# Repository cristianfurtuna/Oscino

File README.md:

# OSCINO - Osciloscop digital interfațat USB cu intrare izolată galvanic
Proiectul nostru constă într-un osciloscop digital interfațat prin USB, capabil să achiziționeze, să proceseze și să afișeze semnale electrice în timp real pe PC.
## Specificații
- in: 5V DC USB-C;<br>
- out: >2 Mbit/s serial UART data;<br>
- Arduino Mega compatible pinout
- sampling rate: ~300 ksa/s;<br>
- AC/DC coupling;<br>
- Galvanically Isolated Frontend with Differential Signal Aquisition;<br>
- 0...230V AC/DC input range using different attenuation stages;<br>
- Attenuator for High Input Voltages;<br>
- UI for PC use;<br>
- timebase and synchronisation (trigger).<br>
## Elaborare etape
- [x] Alegere componente<br>
- [x] Schemă electrică<br>
- [x] Cablaj<br>
- [x] Prototip<br>
- [x] Programare uC<br>
- [x] Programare UI<br>
- [x] Testare<br>
- [x] Elaborare documentație<br>
- [x] Realizare prezentare PowerPoint<br>
## Alegerea unui microcontroller potrivit
- [ ] C8051F120 -> preț: $11.22<br>
- [ ] STM32H743ZIT6 -> preț: $15.23<br>
- [ ] MIMXRT1062DVL6B -> preț: $12.00<br>
- [x] ATMEGA 2560 -> preț: $10.56<br>
## Asamblarea PCB-ului la fabrică este mult prea scumpă pentru a finaliza cablajul (TBD asamblare manuală)

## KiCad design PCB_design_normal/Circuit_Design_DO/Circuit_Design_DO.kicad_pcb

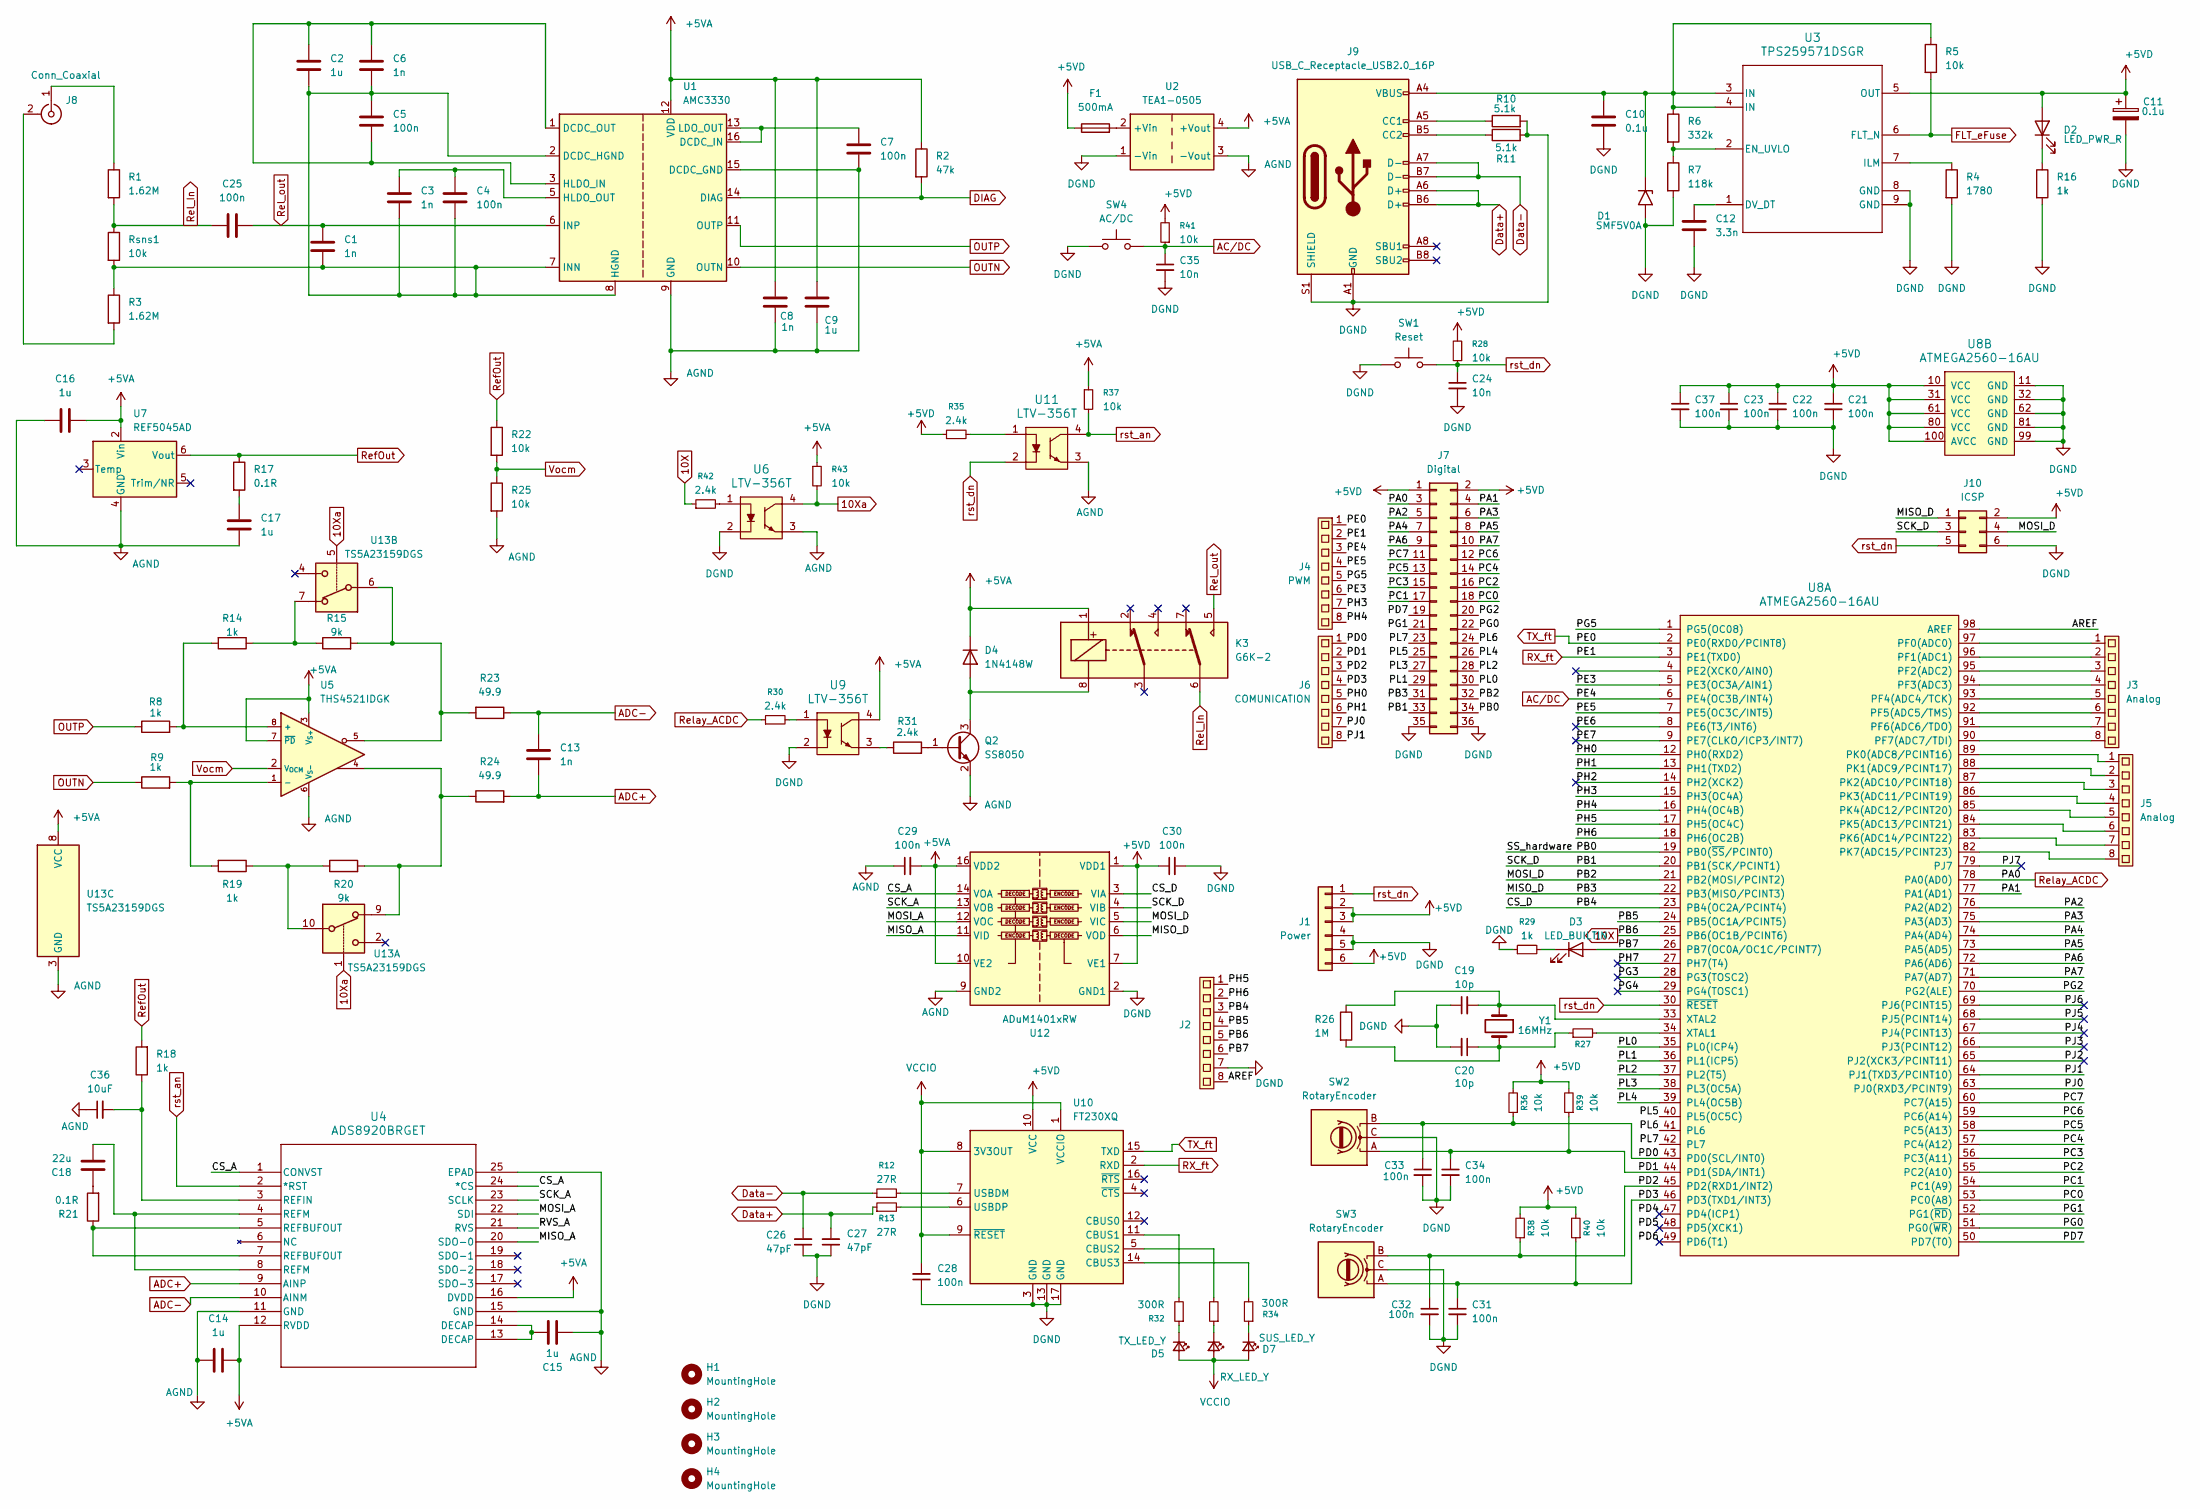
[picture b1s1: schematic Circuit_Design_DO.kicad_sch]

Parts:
C1: 1n; C_0805_2012Metric; JLCPCB Part # C1710
C2, C9, C14, C15, C16, C17: 1u; C_0805_2012Metric; JLCPCB Part # C1712
C3, C6, C8, C13: 1n; C_0805_2012Metric; JLCPCB Part # C1791
C4, C5, C7, C21, C22, C23, C25, C28, C29, C30, C31, C32, C33, C34, C37: 100n; C_0805_2012Metric; JLCPCB Part # C1711
C10, C11: 0.1u; C_0805_2012Metric; JLCPCB Part # C1711
C12: 3.3n; C_0805_2012Metric; JLCPCB Part # C1738
C18: 22u; C_0805_2012Metric; JLCPCB Part # C5674
C19, C20: 10p; C_0805_2012Metric; JLCPCB Part # C107107
C24, C35: 10n; C_0805_2012Metric; JLCPCB Part # C1804
C26, C27: 47pF; C_0805_2012Metric; JLCPCB Part # C14857
C36: 10uF; CP_EIA-6032-28_Kemet-C; JLCPCB Part # C7209
D1: SMF5V0A; D_SMF; JLCPCB Part # C1972946
D2: LED_PWR_R; LED_0805_2012Metric; JLCPCB Part # C86865
D3: LED_BUILTIN; LED_0805_2012Metric; JLCPCB Part # C2904378
D4: 1N4148W; D_SOD-123; JLCPCB Part # C2099
D5: TX_LED_Y; LED_0805_2012Metric; JLCPCB Part # C2904378
D6: RX_LED_Y; LED_0805_2012Metric; JLCPCB Part # C2904378
D7: SUS_LED_Y; LED_0805_2012Metric; JLCPCB Part # C2904378
F1: 500mA; Fuse_0805_2012Metric; JLCPCB Part # C20977
H1, H2, H3, H4: MountingHole; MountingHole_3.2mm_M3_DIN965_Pad_TopBottom
J1: Power; PinHeader_1x06_P2.54mm_Vertical
J2: PinHeader_1x08_P2.54mm_Vertical
J3, J5: Analog; PinHeader_1x08_P2.54mm_Vertical
J4: PWM; PinHeader_1x08_P2.54mm_Vertical
J6: COMUNICATION; PinHeader_1x08_P2.54mm_Vertical
J7: Digital; PinHeader_2x18_P2.54mm_Vertical
J8: Conn_Coaxial; BNC_Amphenol_B6252HB-NPP3G-50_Horizontal; JLCPCB Part # C2837587
J9: USB_C_Receptacle_USB2.0_16P; USB_C_Receptacle_GCT_USB4105-xx-A_16P_TopMnt_Horizontal; JLCPCB Part # C393939
J10: ICSP; PinHeader_2x03_P2.54mm_Vertical
K3: G6K-2; Relay_DPDT_Omron_G6K-2F-Y; JLCPCB Part # C2982926
Q2: SS8050; SOT-23; JLCPCB Part # C2150
R1, R3: 1.62M; R_0805_2012Metric; JLCPCB Part # C189667
R2: 47k; R_0805_2012Metric; JLCPCB Part # C702826
R4: 1780; R_0805_2012Metric; JLCPCB Part # C17397
R5, R22, R25, R28, R36, R37, R38, R39, R40, R41, R43: 10k; R_0805_2012Metric; JLCPCB Part # C702829
R6: 332k; R_0805_2012Metric; JLCPCB Part # C17631
R7: 118k; R_0805_2012Metric; JLCPCB Part # C17427
R8, R9, R14, R16, R18, R19, R29: 1k; R_0805_2012Metric; JLCPCB Part # C702831
R10, R11: 5.1k; R_0805_2012Metric; JLCPCB Part # C702837
R12, R13, R27: 27R; R_0805_2012Metric; JLCPCB Part # C17594
R15, R20: 9k; R_0805_2012Metric; JLCPCB Part # C247026
R17, R21: 0.1R; R_0805_2012Metric; JLCPCB Part # C125639
R23, R24: 49.9; R_0805_2012Metric; JLCPCB Part # C17720
R26: 1M; R_0805_2012Metric; JLCPCB Part # C17514
R30, R31, R35, R42: 2.4k; R_0805_2012Metric; JLCPCB Part # C22370006
R32, R33, R34: 300R; R_0805_2012Metric; JLCPCB Part # C22356757
Rsns1: 10k; R_0805_2012Metric; JLCPCB Part # C702829
SW1: Reset; Switch_Tactile_SMD_6x6mm; JLCPCB Part # C2845322
SW2, SW3: RotaryEncoder; RotaryEncoder_Alps_EC11E_Vertical_H20mm; JLCPCB Part # C370986
SW4: AC/DC; Switch_Tactile_SMD_6x6mm; JLCPCB Part # C2845322
U1: AMC3330; SOIC-16W_7.5x10.3mm_P1.27mm; JLCPCB Part # C5214212
U2: TEA1-0505; Converter_DCDC_TRACO_TEA1-xxxx_THT; JLCPCB Part # C5291394
U3: TPS259571DSGR; DSG0008A; JLCPCB Part # C471038
U4: ADS8920BRGET; RGE24_2P7X2P7_TEX; JLCPCB Part # C1542899
U5: THS4521IDGK; VSSOP-8_3x3mm_P0.65mm; JLCPCB Part # C170157
U6, U9, U11: LTV-356T; SMD-4_4.4x3.85mm_P2.54mm; MPN LTV-356T; Digi-Key_PN 160-1337-1-ND
U7: REF5045AD; SOIC-8_3.9x4.9mm_P1.27mm; JLCPCB Part # C1575525
U8: ATMEGA2560-16AU; TQFP-100_14x14mm; MPN ATMEGA2560-16AU; Digi-Key_PN ATMEGA2560-16AU-ND
U10: FT230XQ; QFN-16-1EP_4x4mm_P0.65mm_EP2.1x2.1mm; JLCPCB Part # C128629
U12: ADuM1401xRW; SOIC-16W_7.5x10.3mm_P1.27mm; JLCPCB Part # C33273
U13: TS5A23159DGS; VSSOP-10_3x3mm_P0.5mm; JLCPCB Part # C42751
Y1: 16MHz; Crystal_SMD_5032-2Pin_5.0x3.2mm; JLCPCB Part # C242221

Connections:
10X: J2.5, R42.1, U8.25 (PB6(OC1B/PCINT6))
10Xa: R43.2, U6.4, U13.1, U13.5
+5VA: C8.1, C9.1, C14.2, C16.1, C29.2, D4.1 (K), K3.1, R2.1, R37.1, R43.1, U1.12 (VDD), U2.4 (+Vout), U4.12 (RVDD), U4.16 (DVDD), U5.3 (V_{S+}), U5.7 (~PD), U7.2 (Vin), U9.4, U12.10 (VE2), U12.16 (VDD2), U13.8 (VCC); also elsewhere on the board
+5VD: C11.1, C21.1, C22.1, C23.1, C30.1, C37.1, D2.2 (A), F1.1, J1.2, J1.3, J1.6, J7.1, J7.2, J10.2, R28.2, R35.1, R36.2, R38.2, R39.2, R40.2, R41.2, U3.5 (OUT), U8.10 (VCC), U8.31 (VCC), U8.61 (VCC), U8.80 (VCC), U8.100 (AVCC), U10.10 (VCC), U12.1 (VDD1), U12.7 (VE1)
/AREF: J2.8, U8.98 (AREF)
/CS_A: U4.1 (CONVST), U4.24 (*CS), U12.14 (VOA)
/CS_D: J2.3, U8.23 (PB4(OC2A/PCINT4)), U12.3 (VIA)
/MISO_A: U4.20 (SDO-0), U12.11 (VID)
/MISO_D: J7.31, J10.1, U8.22 (PB3(MISO/PCINT3)), U12.6 (VOD)
/MOSI_A: U4.22 (SDI), U12.12 (VOC)
/MOSI_D: J7.32, J10.4, U8.21 (PB2(MOSI/PCINT2)), U12.5 (VIC)
/PA1: J7.4, U8.77 (PA1(AD1))
/PA2: J7.5, U8.76 (PA2(AD2))
/PA3: J7.6, U8.75 (PA3(AD3))
/PA4: J7.7, U8.74 (PA4(AD4))
/PA5: J7.8, U8.73 (PA5(AD5))
/PA6: J7.9, U8.72 (PA6(AD6))
/PA7: J7.10, U8.71 (PA7(AD7))
/PB0: J7.34, U8.19 (PB0(~SS/PCINT0))
/PB1: J7.33, J10.3, U8.20 (PB1(SCK/PCINT1)), U12.4 (VIB)
/PB5: J2.4, U8.24 (PB5(OC1A/PCINT5))
/PB7: D3.2 (A), J2.6, U8.26 (PB7(OC0A/OC1C/PCINT7))
/PC0: J7.18, U8.53 (PC0(A8))
/PC1: J7.17, U8.54 (PC1(A9))
/PC2: J7.16, U8.55 (PC2(A10))
/PC3: J7.15, U8.56 (PC3(A11))
/PC4: J7.14, U8.57 (PC4(A12))
/PC5: J7.13, U8.58 (PC5(A13))
/PC6: J7.12, U8.59 (PC6(A14))
/PC7: J7.11, U8.60 (PC7(A15))
/PD0: C33.1, J6.1, R36.1, SW2.B, U8.43 (PD0(SCL/INT0))
/PD1: C34.1, J6.2, R39.1, SW2.A, U8.44 (PD1(SDA/INT1))
/PD2: C32.1, J6.3, R38.1, SW3.B, U8.45 (PD2(RXD1/INT2))
/PD3: C31.1, J6.4, R40.1, SW3.A, U8.46 (PD3(TXD1/INT3))
/PD4: U8.47 (PD4(ICP1))
/PD5: U8.48 (PD5(XCK1))
/PD6: U8.49 (PD6(T1))
/PD7: J7.19, U8.50 (PD7(T0))
/PE3: J4.6, U8.5 (PE3(OC3A/AIN1))
/PE5: J4.4, U8.7 (PE5(OC3C/INT5))
/PE6: U8.8 (PE6(T3/INT6))
/PE7: U8.9 (PE7(CLKO/ICP3/INT7))
/PG0: J7.22, U8.51 (PG0(~WR))
/PG1: J7.21, U8.52 (PG1(~RD))
/PG2: J7.20, U8.70 (PG2(ALE))
/PG3: U8.28 (PG3(TOSC2))
/PG4: U8.29 (PG4(TOSC1))
/PG5: J4.5, U8.1 (PG5(OC08))
/PH0: J6.5, U8.12 (PH0(RXD2))
/PH1: J6.6, U8.13 (PH1(TXD2))
/PH2: U8.14 (PH2(XCK2))
/PH3: J4.7, U8.15 (PH3(OC4A))
/PH4: J4.8, U8.16 (PH4(OC4B))
/PH5: J2.1, U8.17 (PH5(OC4C))
/PH6: J2.2, U8.18 (PH6(OC2B))
/PH7: U8.27 (PH7(T4))
/PJ0: J6.7, U8.63 (PJ0(RXD3/PCINT9))
/PJ1: J6.8, U8.64 (PJ1(TXD3/PCINT10))
/PJ2: U8.65 (PJ2(XCK3/PCINT11))
/PJ3: U8.66 (PJ3(PCINT12))
/PJ4: U8.67 (PJ4(PCINT13))
/PJ5: U8.68 (PJ5(PCINT14))
/PJ6: U8.69 (PJ6(PCINT15))
/PJ7: U8.79 (PJ7)
/PL0: J7.30, U8.35 (PL0(ICP4))
/PL1: J7.29, U8.36 (PL1(ICP5))
/PL2: J7.28, U8.37 (PL2(T5))
/PL3: J7.27, U8.38 (PL3(OC5A))
/PL4: J7.26, U8.39 (PL4(OC5B))
/PL5: J7.25, U8.40 (PL5(OC5C))
/PL6: J7.24, U8.41 (PL6)
/PL7: J7.23, U8.42 (PL7)
/RVS_A: U4.21 (RVS)
/SCK_A: U4.23 (SCLK), U12.13 (VOB)
AC/DC: C35.1, J4.3, R41.1, SW4.2, U8.6 (PE4(OC3B/INT4))
ADC+: C13.2, R24.2, U4.9 (AINP)
ADC-: C13.1, R23.1, U4.10 (AINM)
AGND: C7.2, C8.2, C9.2, C14.1, C15.2, C16.2, C17.2, C29.1, C36.1, Q2.2 (E), R25.2, U1.9 (GND), U1.15 (DCDC_GND), U2.3 (-Vout), U4.11 (GND), U4.15 (GND), U4.25 (EPAD), U4.V, U5.6 (V_{S-}), U6.3, U7.4 (GND), U11.3, U12.9 (GND2), U12.15 (GND2), U13.3 (GND); also elsewhere on the board
DGND: C10.2, C11.2, C12.2, C19.1, C20.2, C21.2, C22.2, C23.2, C24.2, C26.1, C27.1, C28.1, C30.2, C31.2, C32.2, C33.2, C34.2, C35.2, C37.2, D1.2 (A2), J1.4, J1.5, J2.7, J7.35, J7.36, J9.A1 (GND), J9.A12 (GND), J9.B1 (GND), J9.B12 (GND), J9.S1 (SHIELD), J10.6, R4.2, R7.2, R10.2, R11.2, R16.2, R29.1, SW1.1, SW2.C, SW3.C, SW4.1, U2.1 (-Vin), U3.8 (GND), U3.9 (GND), U3.V, U6.2, U8.11 (GND), U8.32 (GND), U8.62 (GND), U8.81 (GND), U8.99 (GND), U9.2, U10.3 (GND), U10.13 (GND), U10.17 (GND), U12.2 (GND1), U12.8 (GND1)
DIAG: R2.2, U1.14 (DIAG)
Data+: C27.2, J9.A6 (D+), J9.B6 (D+), R13.1
Data-: C26.2, J9.A7 (D-), J9.B7 (D-), R12.1
FLT_eFuse: R5.2, U3.6 (FLT_N)
unnamed: C15.1, U4.13 (DECAP), U4.14 (DECAP)
unnamed: C17.1, R17.2
unnamed: C18.1, R21.2
unnamed: C18.2, U4.4 (REFM), U4.8 (REFM)
unnamed: C20.1, R26.2, R27.1, Y1.2
unnamed: C10.1, D1.1 (A1), J9.A4 (VBUS), J9.A9 (VBUS), J9.B4 (VBUS), J9.B9 (VBUS), R5.1, R6.1, U3.3 (IN), U3.4 (IN)
unnamed: D2.1 (K), R16.1
unnamed: D3.1 (K), R29.2
unnamed: D4.2 (A), K3.8, Q2.3 (C)
unnamed: D5.1 (K), R32.1
unnamed: D6.1 (K), R33.1
unnamed: D7.1 (K), R34.1
unnamed: J8.2 (Ext), R3.2
unnamed: J8.1 (In), R1.1
unnamed: J9.A5 (CC1), R10.1
unnamed: J9.B5 (CC2), R11.1
unnamed: Q2.1 (B), R31.2
unnamed: R14.1, R15.1, U13.7
unnamed: R15.2, R23.2, U5.5, U13.6
unnamed: R19.1, R20.1, U13.10
unnamed: R20.2, R24.1, U5.4, U13.9
unnamed: R21.1, U4.5 (REFBUFOUT), U4.7 (REFBUFOUT)
unnamed: R30.2, U9.1
unnamed: R31.1, U9.3
unnamed: R35.2, U11.1
unnamed: R42.2, U6.1
unnamed: C1.2, C2.2, C3.2, C4.2, C5.1, C6.2, R3.1, Rsns1.2, U1.2 (DCDC_HGND), U1.7 (INN), U1.8 (HGND)
unnamed: C7.1, U1.13 (LDO_OUT), U1.16 (DCDC_IN)
unnamed: C2.1, C5.2, C6.1, U1.1 (DCDC_OUT), U1.3 (HLDO_IN)
unnamed: C3.1, C4.1, U1.5 (HLDO_OUT)
unnamed: F1.2, U2.2 (+Vin)
unnamed: C12.1, U3.1 (DV_DT)
unnamed: R6.2, R7.1, U3.2 (EN_UVLO)
unnamed: R4.1, U3.7 (ILM)
unnamed: C36.2, R18.1, U4.3 (REFIN)
unnamed: R8.2, R14.2, U5.8 (+)
unnamed: R9.2, R19.2, U5.1 (-)
unnamed: J3.1, U8.97 (PF0(ADC0))
unnamed: J3.2, U8.96 (PF1(ADC1))
unnamed: J3.3, U8.95 (PF2(ADC2))
unnamed: J3.4, U8.94 (PF3(ADC3))
unnamed: J3.5, U8.93 (PF4(ADC4/TCK))
unnamed: J3.6, U8.92 (PF5(ADC5/TMS))
unnamed: J3.7, U8.91 (PF6(ADC6/TDO))
unnamed: J3.8, U8.90 (PF7(ADC7/TDI))
unnamed: J5.1, U8.89 (PK0(ADC8/PCINT16))
unnamed: J5.2, U8.88 (PK1(ADC9/PCINT17))
unnamed: J5.3, U8.87 (PK2(ADC10/PCINT18))
unnamed: J5.4, U8.86 (PK3(ADC11/PCINT19))
unnamed: J5.5, U8.85 (PK4(ADC12/PCINT20))
unnamed: J5.6, U8.84 (PK5(ADC13/PCINT21))
unnamed: J5.7, U8.83 (PK6(ADC14/PCINT22))
unnamed: J5.8, U8.82 (PK7(ADC15/PCINT23))
unnamed: R27.2, U8.34 (XTAL1)
unnamed: C19.2, R26.1, U8.33 (XTAL2), Y1.1
unnamed: R32.2, U10.11 (CBUS1)
unnamed: R33.2, U10.5 (CBUS2)
unnamed: R34.2, U10.14 (CBUS3)
unnamed: R12.2, U10.7 (USBDM)
unnamed: R13.2, U10.6 (USBDP)
OUTN: R9.1, U1.10 (OUTN)
OUTP: R8.1, U1.11 (OUTP)
RX_ft: J4.2, U8.3 (PE1(TXD0)), U10.2 (RXD)
RefOut: R17.1, R18.2, R22.1, U7.6 (Vout)
Rel_In: C25.1, K3.6, R1.2, Rsns1.1
Rel_out: C1.1, C25.2, K3.5, U1.6 (INP)
Relay_ACDC: J7.3, R30.1, U8.78 (PA0(AD0))
TX_ft: J4.1, U8.2 (PE0(RXD0/PCINT8)), U10.15 (TXD)
VCCIO: C28.2, D5.2 (A), D6.2 (A), D7.2 (A), U10.1 (VCCIO), U10.8 (3V3OUT), U10.9 (~RESET)
Vocm: R22.2, R25.1, U5.2 (V_{OCM})
rst_an: R37.2, U4.2 (*RST), U11.4
rst_dn: C24.1, J1.1, J10.5, R28.1, SW1.2, U8.30 (~RESET), U11.2

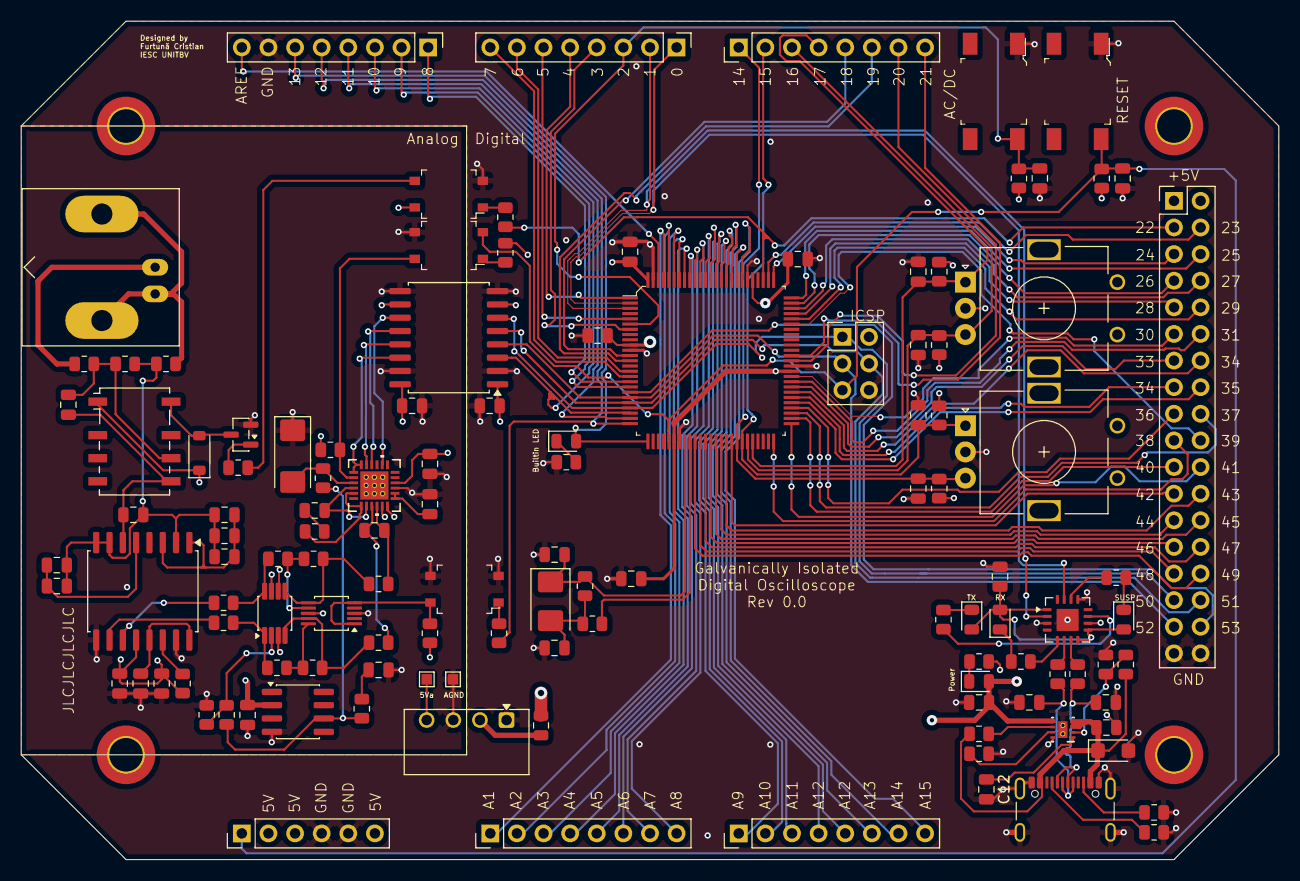
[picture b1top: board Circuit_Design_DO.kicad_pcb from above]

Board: 4 copper layers, 120.0 x 80.0 mm, 125 parts (0 on the bottom side), 139 nets.

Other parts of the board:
5Va: TestPoint_Pad_1.0x1.0mm
AGND: TestPoint_Pad_1.0x1.0mm

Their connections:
+5VA: 5Va.1; also elsewhere on the board
AGND: AGND.1; also elsewhere on the board

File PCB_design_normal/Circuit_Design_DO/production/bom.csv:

Designator,Footprint,Quantity,Value,LCSC Part #
C1,0805,1,1n,C1710
"C10, C11",0805,2,0.1u,C1711
C12,0805,1,3.3n,C1738
"C13, C3, C6, C8",0805,4,1n,C1791
"C14, C15, C16, C17, C2, C9",0805,6,1u,C1712
C18,0805,1,22u,C5674
"C19, C20",0805,2,10p,C107107
"C21, C22, C23, C25, C28, C29, C30, C31, C32, C33, C34, C37, C4, C5, C7",0805,15,100n,C1711
"C24, C35",0805,2,10n,C1804
"C26, C27",0805,2,47pF,C14857
C36,CP_EIA-6032-28_Kemet-C,1,10uF,C7209
D1,D_SMF,1,SMF5V0A,C1972946
D2,0805,1,LED_PWR_R,C86865
D3,0805,1,LED_BUILTIN,C2904378
D4,D_SOD-123,1,1N4148W,C2099
D5,0805,1,TX_LED_Y,C2904378
D6,0805,1,RX_LED_Y,C2904378
D7,0805,1,SUS_LED_Y,C2904378
F1,0805,1,500mA,C20977
J1,PinHeader_1x06_P2.54mm_Vertical,1,Power,
J10,PinHeader_2x03_P2.54mm_Vertical,1,ICSP,
J2,PinHeader_1x08_P2.54mm_Vertical,1,~,
"J3, J5",PinHeader_1x08_P2.54mm_Vertical,2,Analog,
J4,PinHeader_1x08_P2.54mm_Vertical,1,PWM,
J6,PinHeader_1x08_P2.54mm_Vertical,1,COMUNICATION,
J7,PinHeader_2x18_P2.54mm_Vertical,1,Digital,
J8,BNC_Amphenol_B6252HB-NPP3G-50_Horizontal,1,Conn_Coaxial,C2837587
J9,USB_C_Receptacle_GCT_USB4105-xx-A_16P_TopMnt_Horizontal,1,USB_C_Receptacle_USB2.0_16P,C393939
K3,Relay_DPDT_Omron_G6K-2F-Y,1,G6K-2,C2982926
Q2,SOT-23,1,SS8050,C2150
"R1, R3",0805,2,1.62M,C189667
"R10, R11",0805,2,5.1k,C702837
"R12, R13, R27",0805,3,27R,C17594
"R14, R16, R18, R19, R29, R8, R9",0805,7,1k,C702831
"R15, R20",0805,2,9k,C247026
"R17, R21",0805,2,0.1R,C125639
R2,0805,1,47k,C702826
"R22, R25, R28, R36, R37, R38, R39, R40, R41, R43, R5, RSNS1",0805,12,10k,C702829
"R23, R24",0805,2,49.9,C17720
R26,0805,1,1M,C17514
"R30, R31, R35, R42",0805,4,2.4k,C22370006
"R32, R33, R34",0805,3,300R,C22356757
R4,0805,1,1780,C17397
R6,0805,1,332k,C17631
R7,0805,1,118k,C17427
SW1,Switch_Tactile_SMD_6x6mm,1,Reset,C2845322
"SW2, SW3",RotaryEncoder_Alps_EC11E_Vertical_H20mm,2,RotaryEncoder,C370986
SW4,Switch_Tactile_SMD_6x6mm,1,AC/DC,C2845322
U1,SOIC-16W_7.5x10.3mm_P1.27mm,1,AMC3330,C5214212
U10,QFN-16-1EP_4x4mm_P0.65mm_EP2.1x2.1mm,1,FT230XQ,C128629
"U11, U6, U9",SMD-4_4.4x3.85mm_P2.54mm,3,LTV-356T,C10804
U12,SOIC-16W_7.5x10.3mm_P1.27mm,1,ADuM1401xRW,C33273
U13,VSSOP-10_3x3mm_P0.5mm,1,TS5A23159DGS,C42751
U2,Converter_DCDC_TRACO_TEA1-xxxx_THT,1,TEA1-0505,C5291394
U3,DSG0008A,1,TPS259571DSGR,C471038
U4,RGE24_2P7X2P7_TEX,1,ADS8920BRGET,C1542899
U5,VSSOP-8_3x3mm_P0.65mm,1,THS4521IDGK,C170157
U7,SOIC-8_3.9x4.9mm_P1.27mm,1,REF5045AD,C1575525
U8,TQFP-100_14x14mm,1,ATMEGA2560-16AU,C22460
Y1,Crystal_SMD_5032-2Pin_5.0x3.2mm,1,16MHz,C242221

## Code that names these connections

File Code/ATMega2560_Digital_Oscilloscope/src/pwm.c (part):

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 * Implements a small HAL to control PWM channels on ATmega2560 (Arduino Mega mapping).
 *
 * Mapping used (Arduino Mega common mapping):
 * Timer0: OC0A = D13 (PB7), OC0B = D4 (PG5)
 * Timer1: OC1A = D11 (PB5), OC1B = D12 (PB6)
 * Timer2: OC2A = D10 (PB4), OC2B = D9  (PH6)
 * Timer3: OC3A = D5  (PE3), OC3B = D2  (PE4), OC3C = D3  (PE5)
 * Timer4: OC4A = D6  (PH3), OC4B = D7  (PH4), OC4C = D8  (PH5)
 * Timer5: RESERVED (used by millis/timekeeping); PWM on D44/D45/D46 disabled in this HAL
 *
 * This mapping follows Arduino Mega documentation and common pin mapping references. :contentReference[oaicite:1]{index=1}
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     * the addresses match &PORTx below.
     *
     * Timer0
     *  OC0A = PB7 -> PORTB, bit 7  (D13)
     *  OC0B = PG5 -> PORTG, bit 5  (D4)
     */
    if (IS_PIN(&PORTB, 7))
    {
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    }

    /* Timer1
     *  OC1A = PB5 (D11)
     *  OC1B = PB6 (D12)
     */
    if (IS_PIN(&PORTB, 5))
    {
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    /* OC1C not commonly wired to Arduino digital pins on Mega; skip unless needed */

    /* Timer2
     *  OC2A = PB4 (D10)
     *  OC2B = PH6 (D9)
     */
    if (IS_PIN(&PORTB, 4))
    {
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        return out;
    }

    /* Timer3 (PE3, PE4, PE5) -> D5 (A), D2 (B), D3 (C) */
    if (IS_PIN(&PORTE, 3))
    {
        out.timer = 3;
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        return out;
    }

    /* Timer4 (PH3, PH4, PH5) -> D6 (A), D7 (B), D8 (C) */
    if (IS_PIN(&PORTH, 3))
    {
        out.timer = 4;
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
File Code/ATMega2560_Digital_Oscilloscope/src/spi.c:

#include <stdio.h>
#include <avr/io.h>
#include "spi.h"
#include "uart.h"

void SPI_MasterInit(void)
{
    // Set MOSI, SS and SCK output, all others input
    DDRB |= (1 << PB2) | (1 << PB1) | (1 << PB0); // MOSI - PB2, SCK - PB1
    // Enable SPI, Master, set clock rate fck/16 (was 1 << SPR0)
    PORTB |= (1 << PB0);                           // Keep board in Master mode
    SPCR = (1 << SPE) | (1 << MSTR) | (1 << SPR0); // SPCR - SPI control register
    SPSR |= (1 << SPI2X);
}

uint8_t SPI_MasterTransmit(uint8_t data)
{
    // Start transmission; load byte into data register
    SPDR = data; // SPDR - SPI data register
    // Wait for transmission to complete
    while (!(SPSR & (1 << SPIF)))
        ;        // SPSR - SPI status register ; SPIF - SPI Interrupt Flag
    return SPDR; // read received byte after transmission
}

void SPI_SlaveInit(void)
{
    // SET MISO output, all others input
    DDRB |= (1 << PB3); // MISO - PB3
    // Enable SPI
    SPCR = (1 << SPE); // SPCR - SPI control register
}

uint8_t SPI_SlaveReceive(void)
{
    // Wait for reception complete
    while (!(SPSR & (1 << SPIF)))
        ;        // SPSR - SPI status register ; SPIF - SPI Interrupt Flag
    return SPDR; // SPDR - SPI data register
}

// Read data from ADC
uint8_t SPI_Read_MCP3008_8bit(uint8_t channel)
{
    // CS Low
    PORTB &= ~(1 << PB0);

    // Send Start Byte (0x01)
    SPDR = 0x01;
    while (!(SPSR & (1 << SPIF)))
        ;

    // Send config byte si select channel
    SPDR = 0x80 | (channel << 4);
    while (!(SPSR & (1 << SPIF)))
        ;
    uint8_t high = SPDR; // MSB data

    // Send dummy byte pentru a primii ultimii biti ai conversiei
    SPDR = 0x00;
    while (!(SPSR & (1 << SPIF)))
        ;
    uint8_t low = SPDR; // LSB data

    // CS High
    PORTB |= (1 << PB0);

    // Concatenam high si low
    uint16_t result = ((high & 0x03) << 8) | low;
    // Shiftare la dreapta pentru a pastra doar 1 byte
    // La frecvente mari, de regula ultimii 2 biti sunt zgomotosi
    return (uint8_t)(result >> 2);
}

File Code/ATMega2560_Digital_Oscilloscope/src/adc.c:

#include "adc.h"
#include <avr/io.h>
#include <avr/interrupt.h>
#include <util/atomic.h>

/* ---------- Private state ---------- */
static volatile uint16_t s_result;
static volatile uint8_t  s_last_channel;
static volatile uint8_t  s_ready;           /* 0 = no new sample, 1 = new sample available */
static ADC_Callback      s_cb = 0;

/* ---------- Helpers ---------- */
static void adc_disable_digital_buffer(uint8_t channel) {
    if (channel < 8) {
        DIDR0 |= _BV(channel);          // ADC0D..ADC7D
    } else if (channel < 16) {
        DIDR2 |= _BV(channel - 8);      // ADC8D..ADC15D
    }
}

/* Map your GPIO_Pin (from gpio.h) to ADC channel (0..15).
 * On Mega: A0..A7 = PF0..PF7 => ADC0..ADC7; A8..A15 = PK0..PK7 => ADC8..ADC15. */
static int8_t adc_channel_from_pin(GPIO_Pin p) {
    if (p.port == &PORTF) return (int8_t)p.bit;          // 0..7
    if (p.port == &PORTK) return (int8_t)(8 + p.bit);    // 8..15
    return -1;
}

/* Select channel safely when ADC is idle. */
static inline void adc_select_channel(uint8_t channel) {
    if (channel & 0x08) ADCSRB |=  _BV(MUX5);  // channels 8..15
    else                ADCSRB &= ~_BV(MUX5);  // channels 0..7
    /* Keep REFS1:0 and ADLAR; set low 3 MUX bits (0..7 within bank). */
    ADMUX = (ADMUX & 0xE0) | (channel & 0x07);
}

/* ---------- Public API ---------- */
void ADC_set_reference(ADC_Reference ref) {
    /* Keep ADLAR=0 (right-adjust). Only change REFS1:0. */
    ADMUX = (ADMUX & ~(_BV(REFS1) | _BV(REFS0))) | ref;
    /* Note: first sample after changing Vref may be inaccurate. */
}

void ADC_init(ADC_Reference ref, uint8_t prescaler_bits) {
    /* Power up ADC clock domain. */
    PRR0 &= ~_BV(PRADC);

    /* Reference + right-adjust + clear MUX bits initially. */
    ADMUX  = (ref & (_BV(REFS1) | _BV(REFS0))); /* ADLAR=0 */
    ADCSRB = 0;                                 /* MUX5=0, ADTS=0 (no auto trigger) */

    /* Prescaler & enable; also enable interrupt (ADIE). */
    ADCSRA = _BV(ADEN) | _BV(ADIE) |
             (prescaler_bits & (_BV(ADPS2)|_BV(ADPS1)|_BV(ADPS0)));

    /* Clear any pending flag before first start. */
    ADCSRA |= _BV(ADIF);

    s_ready = 0;
}

bool ADC_start(uint8_t channel) {
    if (channel > 15) return false;

    /* If a conversion is ongoing, don't disturb ADMUX (datasheet: ADMUX is locked during conversion). */
    if (ADCSRA & _BV(ADSC)) return false;

    adc_disable_digital_buffer(channel);
    adc_select_channel(channel);

    s_last_channel = channel;
    s_ready = 0;

    /* Clear completion flag; then start single conversion. */
    ADCSRA |= _BV(ADIF);
    ADCSRA |= _BV(ADSC);
    return true;
}

bool ADC_start_pin(GPIO_Pin p) {
    int8_t ch = adc_channel_from_pin(p);
    if (ch < 0) return false;
    return ADC_start((uint8_t)ch);
}

bool ADC_busy(void) {
    return (ADCSRA & _BV(ADSC)) != 0;
}

bool ADC_result_ready(void) {
    return s_ready != 0;
}

bool ADC_get(uint16_t *out) {
    uint16_t v;
    uint8_t have = 0;

    ATOMIC_BLOCK(ATOMIC_RESTORESTATE) {
        if (s_ready) {
            v = s_result;
            s_ready = 0;         /* consume the sample */
            have = 1;
        }
    }

    if (have && out) *out = v;
    return (bool)have;
}

void ADC_set_callback(ADC_Callback cb) {
    ATOMIC_BLOCK(ATOMIC_RESTORESTATE) {
        s_cb = cb;
    }
}

/* ---------- Compatibility (blocking wrappers) ----------
 * These block until a fresh result arrives via the ISR.
 * REQUIREMENT: global interrupts must be enabled (sei()). */
uint16_t ADC_read(uint8_t channel) {
    while (!ADC_start(channel)) {
        /* Busy; wait for current conversion to finish. */
        /* If interrupts are disabled, this would deadlock — ensure sei() is used by the caller. */
    }
    while (!ADC_result_ready()) { /* wait for ISR to complete */ }
    uint16_t v = 0;
    (void)ADC_get(&v);
    return v;
}

uint16_t ADC_read_pin(GPIO_Pin p) {
    int8_t ch = adc_channel_from_pin(p);
    if (ch < 0) return 0xFFFFu;
    return ADC_read((uint8_t)ch);
}

/* ---------- ISR ---------- */
ISR(ADC_vect) {
    /* Read result (ADCL first, then ADCH). Using ADCW performs correct sequence. */
    uint16_t v = ADCW;

    s_result = v;
    s_ready  = 1;

    /* Clear interrupt flag explicitly (write 1 to ADIF). */
    ADCSRA |= _BV(ADIF);

    /* Optional user callback (keep it very short/ISR-safe). */
    if (s_cb) {
        s_cb(v, s_last_channel);
    }
}

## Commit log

2025-10-09 initial folder structure
2025-10-16 Update README.md
    Updated project description and specifications for Nibiru.
2025-10-16 Format specifications with HTML line breaks
    Updated specifications format with HTML line breaks.
2025-10-16 Revise output details and add project development steps
    Updated output specification and added project stages.
2025-10-16 Update presentation task description in README
2025-10-16 Add mention of Windows UI Interface/Python script
2025-10-20 Added project files with HAL for different functions
2025-10-23 Added preliminary components list and Hardware design timeline
2025-10-25 Components Excel sheet
    Added Excel sheet for components alongside prices and links
2025-10-30 Added new folder for components and initial commit of schematic work
2025-10-30 Renamed Componenete.xlsx to Components.xlsx and updated Components.txt
2025-10-30 Renamed folder Extra_components to Components and moved all related files in it, added datasheets
2025-10-30 Add microcontroller selection section to README
    Added section for microcontroller selection with options and prices.
2025-11-02 Added simple SPI communication
    -added simple Master/Slave SPI behaviour
    -modified formatting in main.c
2025-11-03 Updated SS pin
    Keep Slave Select in 1 so board stays in Master mode
2025-11-03 Added minor comments
2025-11-06 Added test code for external ADC
    configuring ADC and reading data from a channel
2025-11-06 Added datasheet for external 10 bitADC
2025-11-20 Testing ADC data display on a software graph
2025-12-04 Updated schematic design (missing some headers for now), started layout design
2025-12-10 Added a folder for a normal pcb design, the other one is Arduino style, started an Arduino PCB layout with headers, repaired schematic mistakes
2025-12-13 Outlined layout for non-Arduino PCB, started to place components
2025-12-13 Power circuits and microcontroller+oscillator placement
2025-12-14 Added frontend circuits, powerplanes, changed relay component
2025-12-29 Almost done PCB design and final hardware checks
2025-12-29 Finished PCB and electronic design
2025-12-29 Final touches
2025-12-29 Update Cablaj status and add PCB assembly note
2026-01-05 test python GUI
2026-01-14 added Doc template
2026-01-14 Added Slides folder
2026-01-14 Added Hardware documentation (unfinished)
2026-01-15 modified gui
2026-01-15 Added slides file
2026-01-15 modificari spi
2026-01-15 Added Hardware spec on slides
2026-01-15 Mark project tasks as completed in README
    Updated the project tasks to reflect completed items.
2026-01-16 Modificari finale
2026-01-16 slides updated
2026-01-16 final final update
2026-03-25 removed secondary design
2026-03-27 Rename project from Nibiru to OSCINO
2026-03-27 Revise README with updated specifications and features
    Updated project description and specifications for the OSCINO oscilloscope.
2026-03-27 Enhance description of Galvanically Isolated Frontend
